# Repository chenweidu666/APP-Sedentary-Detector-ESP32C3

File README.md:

# Sedentary Detector ESP32 - 久坐检测器

基于 **ESP32-WROOM-32** + **GY-87**（MPU6050）+ **OLED** 的椅子久坐检测器载板方案。本仓库**仅保留硬件**（BOM、接线、KiCad）；固件与联调在独立项目中完成。

**策略**：现成模块 + 定制载板 PCB 插接互连；PM11 锂电包供电（USB 充电，模块自带开关）。

**载板布线节奏**：KiCad 已完成原理图、布局与网络分配；**PCB 尚未布线**。固件与算法仍在 [03](../../03-ESP32-OLED-Button-Demo) / [04](../../04-MCU-GY87-Debug) 中联调，接口与引脚稳定后再走线、DRC、打样，避免返工。

## 当前进度

| 模块 | 状态 |
|------|------|
| 硬件方案 | ✅ MCU + GY-87 + OLED + PM11（无载板按键/开关） |
| 原理图 | ✅ v0.6（J1–J4 网络） |
| 载板 PCB | 🔧 v0.4 已布局 + 网络分配 + J2 对齐；**未布线**（等软件联调稳定后走线打样） |
| GY-87 / IMU 联调 | 🔧 [04-MCU-GY87-Debug](../../04-MCU-GY87-Debug) 调试中 |
| OLED 联调 | 🔧 [03-ESP32-OLED-Button-Demo](../../03-ESP32-OLED-Button-Demo) 调试中 |
| 3D 底座 | ⏳ 待设计 |

## 系统架构

```
         USB 充电
            │
    ┌───────┴────────────────────────────┐
    │  PM11 电源 (自带 ON/OFF)              │
    │       5V / GND                       │
    └───────┬────────────────────────────┘
            │ J3
    ┌───────┴────────────────────────────┐
    │  载板 PCB (100×80)                  │
    │  ┌─────────┐  I2C   ┌──────────┐   │
    │  │ GY-87   │═══════│ ESP32    │   │
    │  │ J2      │       │ DevKitC  │   │
    │  └─────────┘       │ J1       │   │
    │  ┌─────────┐       └──────────┘   │
    │  │ OLED    │═══════ (共享 I2C)     │
    │  │ J4      │                       │
    │  └─────────┘                       │
    └────────────────────────────────────┘
```

检测算法与固件开发见下方**关联软件项目**。

## 文档

| 文档 | 内容 |
|------|------|
| [hardware/HARDWARE.md](hardware/HARDWARE.md) | **硬件权威**：BOM、网络表、模块引脚、电源、PCB 版本 |
| [AGENTS.md](AGENTS.md) | AI / KiCad 自动化工作流 |

### KiCad 载板工程

```bash
kicad hardware/kicad/SedentaryDetector.kicad_pro
```

打样前核对 [hardware/HARDWARE.md §PCB 版本记录](hardware/HARDWARE.md#pcb-版本记录)。

### 关联软件项目（本仓库不含固件源码）

| 项目 | 内容 |
|------|------|
| [03-ESP32-OLED-Button-Demo](../../03-ESP32-OLED-Button-Demo) | SSD1306 OLED + I2C |
| [04-MCU-GY87-Debug](../../04-MCU-GY87-Debug) | GY-87 / MPU6050、久坐检测、BLE |

## 项目结构

```
02-APP-Sedentary-Detector-ESP32/
├── README.md          # 本文件（仓库唯一 README）
├── AGENTS.md
└── hardware/
    ├── HARDWARE.md
    ├── images/
    ├── kicad/
    └── scripts/
```

## 里程碑

| 阶段 | 目标 | 状态 |
|------|------|------|
| M1 模块联调 | 杜邦线验证 GY-87 + OLED（03/04） | 🔧 |
| M2 载板 | 软件稳定后 PCB 布线 → DRC → 打样焊接 | ⏳ |
| M3 整合 | 载板 + 03/04 固件合并产品化 | ⏳ |

## License

MIT

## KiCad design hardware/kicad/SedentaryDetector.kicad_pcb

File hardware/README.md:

# Hardware

载板、模块接线与 KiCad 工程的**唯一权威文档**是 [HARDWARE.md](HARDWARE.md)。

| Path | Description |
|------|-------------|
| [HARDWARE.md](HARDWARE.md) | BOM、网络表、GY-87/OLED/PM11、PCB 版本 |
| [kicad/](kicad/) | `SedentaryDetector.kicad_pro` |
| [images/](images/) | 引脚图与模块照片 |
| [scripts/](scripts/) | `gen_sch.py` 原理图骨架 |

```bash
kicad hardware/kicad/SedentaryDetector.kicad_pro
```

打样前核对 [HARDWARE.md §PCB 版本记录](HARDWARE.md#pcb-版本记录)。

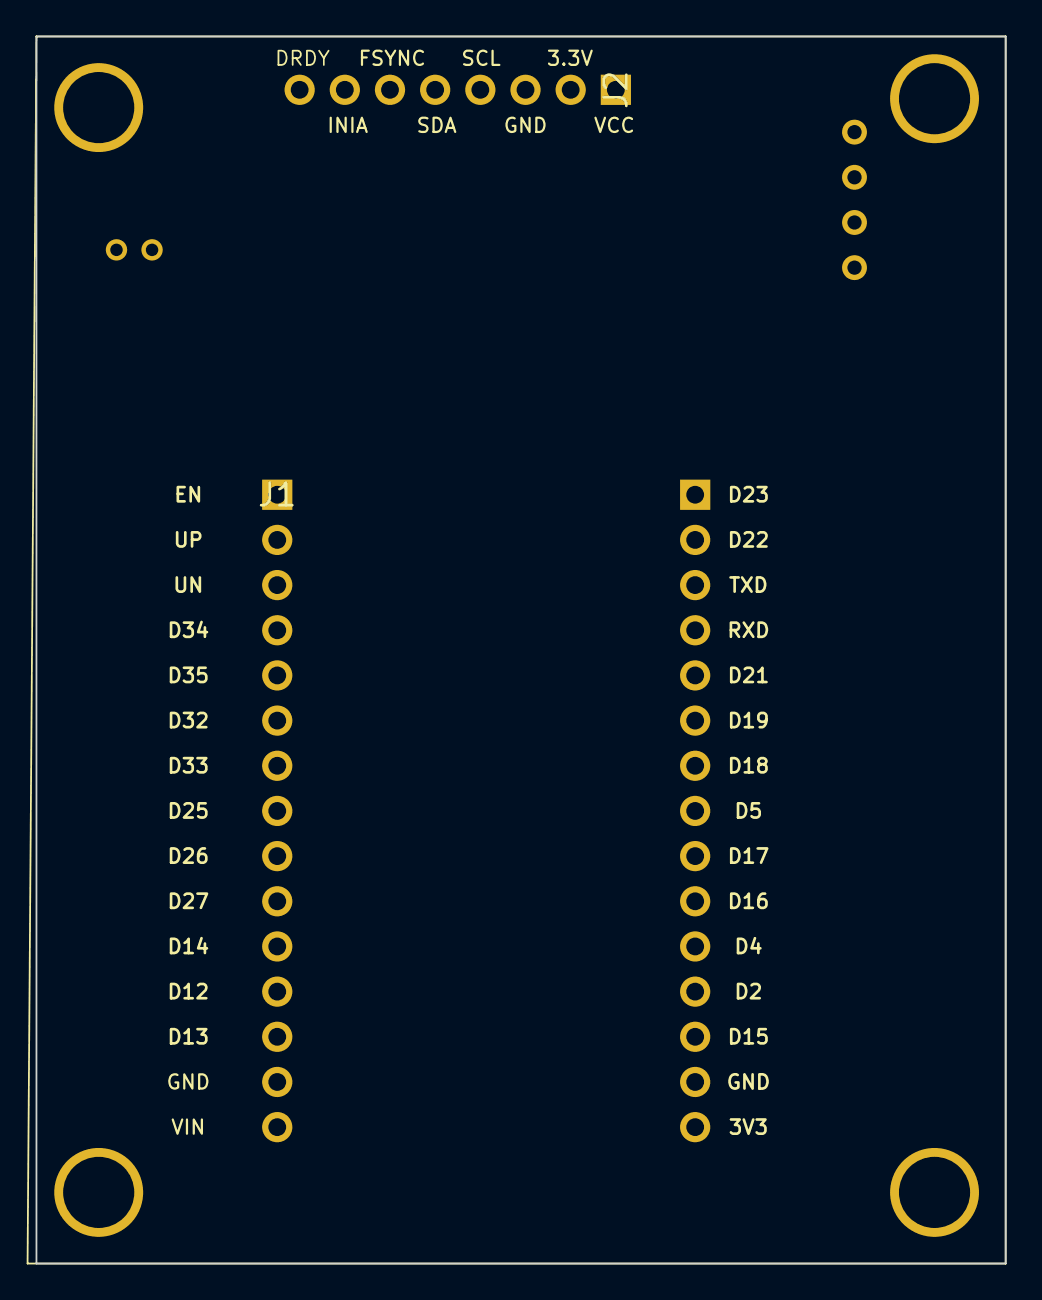
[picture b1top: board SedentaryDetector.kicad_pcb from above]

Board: 2 copper layers, 54.5 x 69.0 mm, 8 parts (0 on the bottom side), 6 nets, no tracks yet.

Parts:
J1: ESP32_2x15
J2: GY-87
J3: POWER_2P
J4: OLED_0.96
MH1, MH2, MH3, MH4: (no value)

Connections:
3V3: J1.30 (3V3), J2.1 (VCC_IN), J4.1
5V: J1.15 (VIN), J3.2
GND: J1.14 (GND), J1.29 (GND), J2.3 (GND), J3.1, J4.2
I2C_SCL: J1.23 (D5), J2.4 (SCL), J4.3
I2C_SDA: J1.26 (D4), J2.5 (SDA), J4.4
MPU_INT: J1.27 (D2), J2.7 (INTA)

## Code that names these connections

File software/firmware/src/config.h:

#pragma once

// GY-87 联调 / 载板 J2：D4=SDA, D5=SCL, D2=INTA（见 hardware/HARDWARE.md）
constexpr int PIN_I2C_SDA = 4;   // D4
constexpr int PIN_I2C_SCL = 5;   // D5
constexpr int PIN_MPU_INT = 2;   // D2，与 DevKit 板载 LED 共用
constexpr int PIN_LED = 2;

constexpr uint8_t MPU_ADDR = 0x68;

constexpr uint8_t OLED_ADDR = 0x3C;
constexpr int OLED_WIDTH = 128;
constexpr int OLED_HEIGHT = 64;

constexpr unsigned long SAMPLE_INTERVAL_MS = 2000;
constexpr int DEBOUNCE_COUNT = 3;
constexpr int SEDENTARY_MINUTES = 45;
constexpr float ANGLE_OCCUPIED_DEG = 1.0f;
constexpr float ANGLE_VACANT_DEG = 0.5f;

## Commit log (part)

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2026-06-19 init: 项目初始化，添加 README 和 .gitignore
2026-06-19 refactor: 改用PM11电池模块(自带充电+升压5V), 移除TP4056, 简化载板设计
2026-06-19 chore: 移除下载的HTML文件
2026-06-19 docs: 载板PCB接线表, 网络表, 立创EDA绘制步骤
2026-06-19 feat: 添加Wokwi仿真项目 (ESP32+MPU6050+LED)
    - diagram.json: 电路连接定义
    - wokwi.toml: Wokwi配置
    - main.cpp: 角度检测+久坐计时固件
    - 更新README进度表和项目结构
2026-06-20 docs: 重构项目文档, 修正成本, 添加模块存档
    - README.md: 项目总览, 修正成本为实际价格(¥91.22)
    - hardware/HARDWARE.md: 硬件设计文档(选型/BOM/接线/供电/PCB/3D底座)
    - firmware/FIRMWARE.md: 固件设计文档(架构/算法/状态机/BLE/电源管理)
    - hardware/module_pages/: 三个核心模块商品页HTML存档
    - esp32-c3-mini.html (¥35.67)
    - mpu6050-gy521.html (¥25.55)
2026-06-20 feat(hardware): Phase 1 - ESP32-C3 + MPU6050 carrier board PCB
    Hardware Design (KiCad 7):
    - J1: ESP32-C3 Mini 2x9 pin header connector
    - J2: MPU6050 GY-521 1x8 pin header connector
    - Board: 80x50mm, 2-layer, 1.6mm FR-4
    - GND copper pour on bottom layer
    - I2C pull-up ready (for Phase 2)
2026-06-20 Add critical routing traces between connectors
    Routes added on F.Cu layer:
    - 3V3: J1.p10 -> J2.p1 (2 segments, 0.254mm)
    - I2C_SDA: J1.p7 -> J2.p4 (1 segment, 0.254mm)
    - I2C_SCL: J1.p8 -> J2.p3 (2 segments, 0.254mm)
    - INT: J1.p5 -> J2.p8 (2 segments, 0.254mm)
    Verified:
2026-06-20 docs(hardware): update troubleshooting with PCB format issues
    Added 3 new issues:
    - #4: Boolean values must be true/false (not yes/no) in KiCad 7
    - #5: Footprint uses tstamp not uuid
    - #6: Pad definitions require tstamp field
    Added best practices section for hand-writing KiCad files
    Recommended workflow: copy from demo → edit in GUI → save
2026-06-20 feat(hardware): regenerate PCB with KiCad 9 Python API
    Replace hand-written S-expression PCB with API-generated file:
    - Uses KiCad 9 AppImage Python API (pcbnew via AppRun)
    - Board: 50x35mm, 2-layer
    - J1: ESP32-C3 Mini 2x9 through-hole header
    - J2: MPU6050 1x8 through-hole header
    - GND zone on B.Cu layer
2026-06-20 docs(hardware): add KiCad 9 Python API troubleshooting
    - Issue #7: KiCad 9 API environment setup (AppRun required)
    - Document API changes: SetPadType→SetAttribute, PAD_ATTRIB_PTH
    - Add recommended KiCad 9 Python workflow
2026-06-20 fix(hardware): correct pin spacing to 2.54mm, add I2C/INT routing
    PCB fixes:
    - Row spacing: 24.5mm -> 2.54mm (standard 0.1in pitch)
    - Board: 50x35mm (per AGENTS.md)
    - J1: 2x15 @ (-15, -17.8)mm
    - J2: 1x8 @ (10, -7.6)mm
    - No overlap between connectors
2026-06-20 chore: add .gitignore for KiCad backup/generated files
2026-06-20 fix(hardware): use absolute pad coordinates, fix connector overlap
    - Use absolute pad positions (not relative to footprint)
    - J1: x=[-13, -10.5], J2: x=[8] - separated by 18.5mm
    - 4 traces: I2C_SDA, I2C_SCL, 3V3, MPU_INT on F.Cu
    - GND copper pour on B.Cu
    - kicad-happy: 0 errors, PCB passes analysis
2026-06-20 fix(hardware): correct J1 row spacing to 23.5mm
    ESP32-WROOM-32 2x15 connector:
    - Row spacing: 23.5mm (between left/right columns)
    - Pin pitch: 2.54mm (vertical, within each column)
    - J1 at x=-18mm (left column), right column at x=-18+23.5=5.5mm
    J2 MPU6050 1x8 at x=12mm
    Routing: I2C_SDA, I2C_SCL, 3V3, MPU_INT
2026-06-20 fix(hardware): clear ratsnest (net assignments deferred to routing phase)
    - Removed all pad net assignments to avoid ratsnest lines
    - Nets still defined for later routing use
    - No blue connection lines on PCB view
2026-06-20 docs: add pcbnew API pitfalls and workflow to AGENTS.md
    - Absolute pad coordinates (KiCad 10 behavior)
    - Clear ratsnest before routing
    - Never hand-write S-expressions
    - Layout-first workflow (place -> verify -> route)
    - ESP32-WROOM-32 dimensions: 23.5mm row spacing
2026-06-20 chore: remove auto-generated DRC report, add to gitignore
2026-06-20 feat(hardware): detailed silk annotations on PCB
    Added silk labels:
    - J1: connector name, pin functions (GND,3V3,INT,SDA,SCL,VIN)
    - J2: pin functions (VCC,GND,SCL,SDA,INT)
    - Row spacing dimension line: 23.5mm
    - Mounting holes: MH1-4 with M3 spec
    - Board info: Project name, size, GND pour note
2026-06-20 fix(schematic): generate valid KiCad 10 schematic
    Replace broken gen_sch.py output with proper KiCad 10 format:
    - J1: 2x15 ESP32-WROOM-32 connector (30 pins, inline symbol)
    - J2: 1x8 MPU6050-GY521 connector (8 pins, inline symbol)
    - Uses tab indentation (KiCad 10 requirement)
    - Pin UUIDs generated properly
    - Exports to PDF successfully
2026-06-20 fix(hardware): silk labels within board bounds, correct PDF export
    - Fix J2 pin label Y coordinates (was using X position by mistake)
    - Adjust all silk positions to stay within 80x50mm board
    - KiCad 10 PDF export: use --mode-single --scale 0 --ibt
2026-06-20 fix(hardware): correct J2 silk positions, update HARDWARE.md with ESP32 pinout
    - J2 MPU6050 labels moved outside module outline
    - HARDWARE.md updated with ESP32-WROOM-32 pinout image
    - Added ESP32 pinout reference image to hardware/images/
2026-06-20 fix(hardware): final PCB layout with clean pin labels
    - Removed J1/J2 reference text, only keep pin labels
    - Added MCU direction arrow (USB side down)
    - J1 (2x15): Left: EN,GPIO15-2; Right: GND,VIN,GPIO23-13,GND
    - J2 (1x8): VCC,GND,SCL,SDA,XDA,XCL,AD0,INT
    - Updated HARDWARE.md with correct pin assignments
2026-06-20 fix(hardware): final clean PCB - only pin labels
    - J1: Left: EN,GPIO15-2; Right: GND,VIN,GPIO23-13,GND
    - J2: VCC,GND,SCL,SDA,XDA,XCL,AD0,INT
    - No J1/J2 titles, no dimension lines, no module outlines
    - B.Cu GND copper pour
2026-06-20 fix(hardware): correct ESP32-WROOM-32 pinout and remove traces
    - Left P1-P15: 3V3,EN,GPIO36-12,GND,VIN (correct order)
    - Right P16-P30: GPIO23-15,GND,3V3,NC
    - J2 P1-P8: VCC,GND,SCL,SDA,XDA,XCL,AD0,INT
    - Removed all routing traces (user will route in KiCad GUI)
    - Added HARDWARE_PINOUT.md documentation
2026-06-20 fix(hardware): correct ESP32 pinout to 15+14 pins per user spec
    PCB silk:
    - Left: P1-P15 (3V3,EN,GPIO36-12,GND,VIN)
    - Right: P16-P29 (GPIO23,22,21,GND,19,18,5,17,16,4,2,15,GND,3V3) - 14 pins
    - J2: P1-P8 (VCC,GND,SCL,SDA,XDA,XCL,AD0,INT)
    - No NC, no traces, no zones
    Docs:
2026-06-20 PCB silk: L-P1~L-P15, R-P1~R-P14, J2-P1~J2-P8 format
2026-06-20 PCB silk: R-P1~R-P15 (both columns 15 labels)
2026-06-20 feat(hardware): enlarge board to 100x80mm, correct pin placement
2026-06-20 chore(hardware): clean up directory structure
2026-06-20 docs(hardware): add MPU6050 GY-521 image
2026-06-20 docs: simplify MPU6050 naming, remove GY-521
2026-06-20 docs: remove all GY-521 references, use MPU6050 only
2026-06-20 docs: restore PM11 power module
2026-06-20 fix(hardware): remove auto Edge.Cuts, add GND pour, fix silk size
2026-06-20 feat(hardware): auto-route 4 signals with spaced channels
2026-06-20 Revert: remove all traces, user to route manually
2026-06-20 Phase 2: routing strategy + net assignments
2026-06-20 Revert: remove Edge.Cuts, user to draw
2026-06-20 docs(sch): add J3 POWER_2P power connector
2026-06-20 feat(hardware): add board outline through MH
2026-06-20 fix(hardware): border 3mm outside MH, 53x68mm
2026-06-20 V0.4: Gerber export ready, J3 power, M4 holes
